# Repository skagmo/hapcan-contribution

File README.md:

HAPCAN contribution
===================

This is a collaboration of work I've done related to my home automation system based on HAPCAN.

HAPCAN is a completely open source home automation system with wired components communicating over CAN bus. It is comparable with KNX, but far cheaper. Due to the open source nature and the use of CAN, it is also much better suited for those interested in making their own modules.

This has no connection with the HAPCAN project, and modules are therefore called "HAPCAN compatible", as they can communicate with HAPCAN devices but are not actual HAPCAN devices. It can rather be seen as a contribution to the HAPCAN community.

--
Jon Petter Skagmo, LA3JPA

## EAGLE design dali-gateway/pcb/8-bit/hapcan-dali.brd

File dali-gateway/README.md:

HAPCAN compatible DALI gateway
==============================

The purpose of this project is to connect a DALI (Digital Addressable Lighting Interface) network with a HAPCAN network, and making it possible to control for example a DALI dimmer by triggering a HAPCAN button module.

Features
--------

Can be indirectly controlled by other CAN nodes. The behaviour is somewhat similar to "memory cells" in HAPCAN, but less flexible due to the differences between HAPCAN and DALI. A given HAPCAN node sending BUTTON frames can indirectly trigger a given DALI address, and enable "Touch DIM" behaviour:

- Short press (under 400 ms): Toggle state of DALI device. As the DALI protocol does not have a toggle command, the gateway keeps track of the state and arc level of all 81 DALI addresses (64 individual, 16 groups, 1 broadcast) to make a DALI dimmer toggle between being off and being set at a given arc level.

- Long press (over 400 ms): Will start dimming the DALI device by sending an arc level command every 100 ms until the button is released, or the maximum or minimum level has been reached.

After the state or arc level of a DALI device has been changed, either through direct or indirect control, the gateway will send the new state and arc level to the CAN bus to update all other nodes.

The gateway can also be directly controlled with an instruction (toggle or set arc level), an arc level (ignored if toggling), and a DALI address.

Firmware project
----------------

The project is written in C for a 32-bit PIC32MX564F128H microcontroller. It is therefore quite different from HAPCAN devices which uses an 8-bit PIC18F26K80, and makes it incompatible with the standard HAPCAN bootloader.

Open the project in Microchip MPLAB X and compile with the XC32 compiler.

| File       | Description |
|:------     |:----------- |
| logic.c    | Contains the gateway logic between DALI and CAN, and HAPCAN related definitions. |
| dali.c     | PIC32 DALI implementation using pin interrupt and timer interrupt. |
| can.c      | CAN initialization and send/receive routines. |

Hardware project
----------------

The schematic and PCB is made in Eagle CAD, and made to fit inside a double DIN rail enclosure similar to those used in the HAPCAN project.

--
Jon Petter Skagmo, LA3JPA, 2016

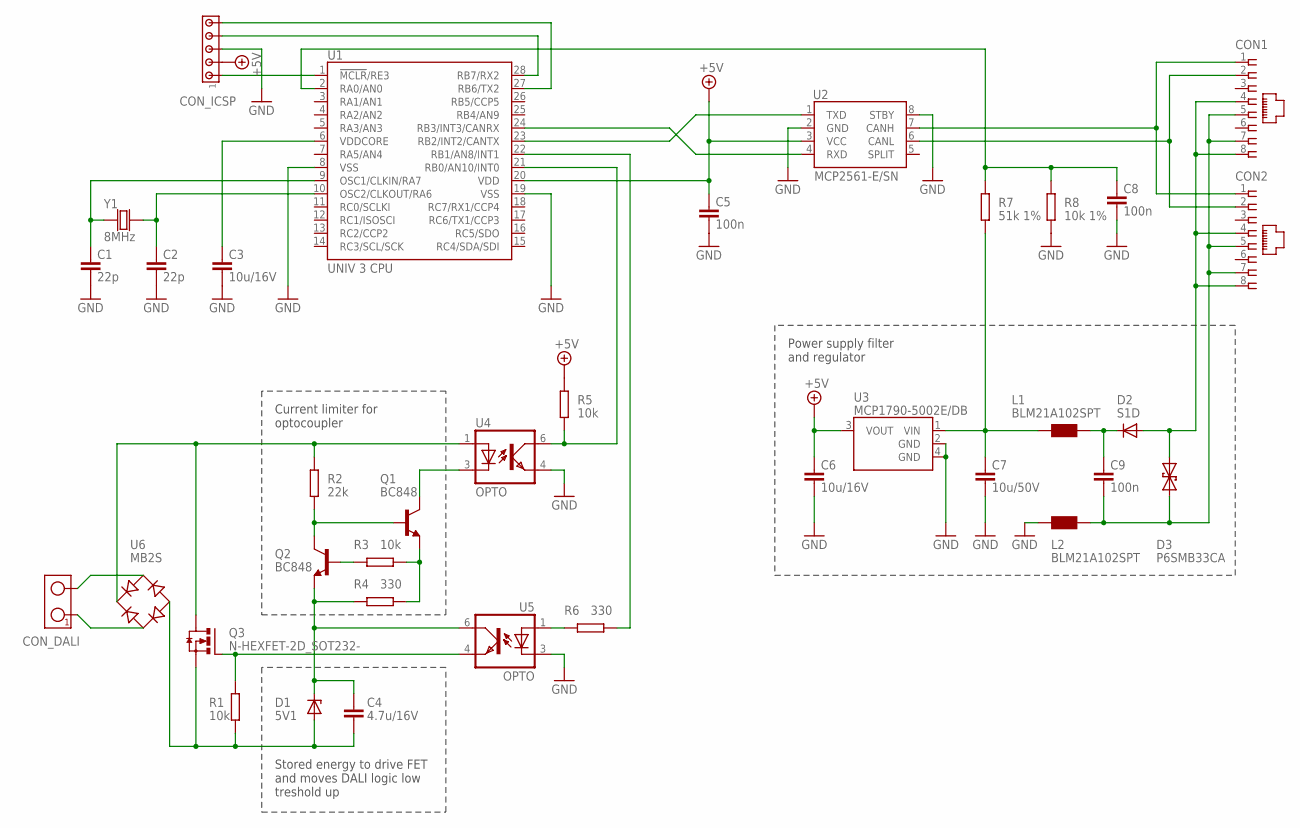
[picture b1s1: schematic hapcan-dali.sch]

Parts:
C1, C2: 22p; 0805
C3, C6: 10u/16V; 0805
C4: 4.7u/16V; 0805
C5, C8, C9: 100n; 0805
C7: 10u/50V; 1210
CON1, CON2: RJ45-SOCKET; RJ45-PCB-SOCKET
CON_DALI: TERMINAL-2; ARK2-5X10,5MM
CON_ICSP: HEADER5; SIP-5
D1: 5V1; SOT23
D2: S1D; DO-214
D3: P6SMB33CA; DO-214_TRANSIL2
L1, L2: BLM21A102SPT; 0805
Q1, Q2: BC848; SOT23
Q3: N-HEXFET-2D_SOT232-; SOT223
R1, R3, R5: 10k; 0805
R2: 22k; 0805
R4, R6: 330; 0805
R7: 51k 1%; 0805
R8: 10k 1%; 0805
U1: UNIV 3 CPU; UNIV3CPU
U2: MCP2561-E/SN; SO-08
U3: MCP1790-5002E/DB; SOT-223
U4, U5: OPTO; TLP185
U6: MB2S; SOIC-4
Y1: 8MHz; CRYSTAL-HC49V

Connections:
+5V: C5.1, C6.1, CON_ICSP.2, R5.1, U1.20 (VDD), U2.3 (VCC), U3.3 (VOUT)
CAN_N: CON1.2, CON2.2, U2.6 (CANL)
CAN_P: CON1.1, CON2.1, U2.7 (CANH)
GND: C1.2, C2.2, C3.2, C5.2, C6.2, C7.2, C8.2, CON_ICSP.3, L2.1, R8.1, U1.8 (VSS), U1.19 (VSS), U2.2 (GND), U2.8 (STBY), U3.2 (GND), U3.4 (GND), U4.4 (EMIT), U5.3 (C)
unnamed: Q1.2 (E), R3.1, R4.2
unnamed: U1.24 (RB3/INT3/CANRX), U2.4 (RXD)
unnamed: U1.23 (RB2/INT2/CANTX), U2.1 (TXD)
unnamed: Q2.1 (B), R3.2
unnamed: C9.1, D2.C, L1.2
unnamed: Q1.1 (B), Q2.3 (C), R2.1
unnamed: C4.2, D1.1 (A), Q3.3 (S), R1.1, U6.-
unnamed: CON_ICSP.1, U1.1 (!MCLR!/RE3)
unnamed: CON1.4, CON1.8, CON2.4, CON2.8, D2.A, D3.C (2)
unnamed: CON_ICSP.4, U1.28 (RB7/RX2)
unnamed: Q1.3 (C), U4.3 (C)
unnamed: CON_ICSP.5, U1.27 (RB6/TX2)
unnamed: C2.1, U1.10 (OSC2/CLKOUT/RA6), Y1.2
unnamed: C8.1, R7.2, R8.2, U1.2 (RA0/AN0)
unnamed: C7.1, L1.1, R7.1, U3.1 (VIN)
unnamed: CON_DALI.1, U6.~1 (AC1)
unnamed: CON_DALI.2, U6.~2 (AC2)
unnamed: R6.1, U1.22 (RB1/AN8/INT1)
unnamed: C9.2, CON1.5, CON1.7, CON2.5, CON2.7, D3.A (1), L2.2
unnamed: Q3.1 (G), R1.2, U5.4 (EMIT)
unnamed: Q3.2 (D), Q3.4 (D), R2.2, U4.1 (A), U6.+
unnamed: R5.2, U1.21 (RB0/AN10/INT0), U4.6 (COL)
unnamed: C4.1, D1.3 (C), Q2.2 (E), R4.1, U5.6 (COL)
unnamed: R6.2, U5.1 (A)
unnamed: C1.1, U1.9 (OSC1/CLKIN/RA7), Y1.1
unnamed: C3.1, U1.6 (VDDCORE)

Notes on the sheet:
Stored energy to drive FET and moves DALI logic low treshold up
Current limiter for optocoupler
Power supply filter and regulator

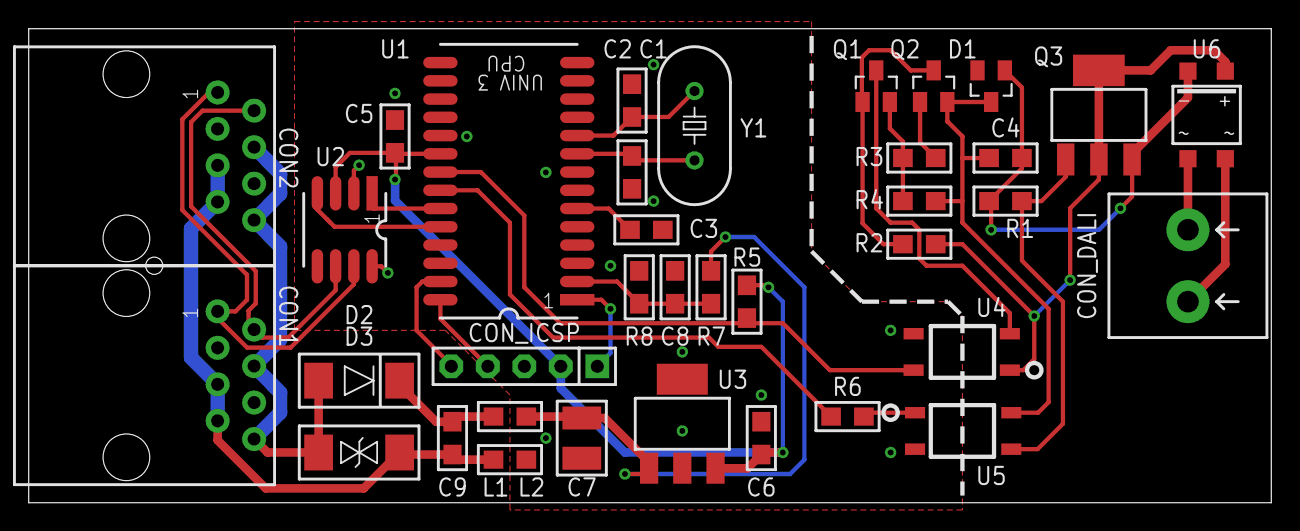
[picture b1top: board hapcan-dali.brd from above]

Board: 4 copper layers, 86.5 x 33.0 mm, 36 parts (0 on the bottom side), 30 nets.

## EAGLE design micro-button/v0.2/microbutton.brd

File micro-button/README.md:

HAPCAN compatible micro button interface
========================================

A firmware compatible re-make of the HAPCAN button module.

I made it because I wanted a board with connectors and smaller outline. Version 2 runs on 3.3 V and uses a small switch mode buck converter to minimize power consumption.

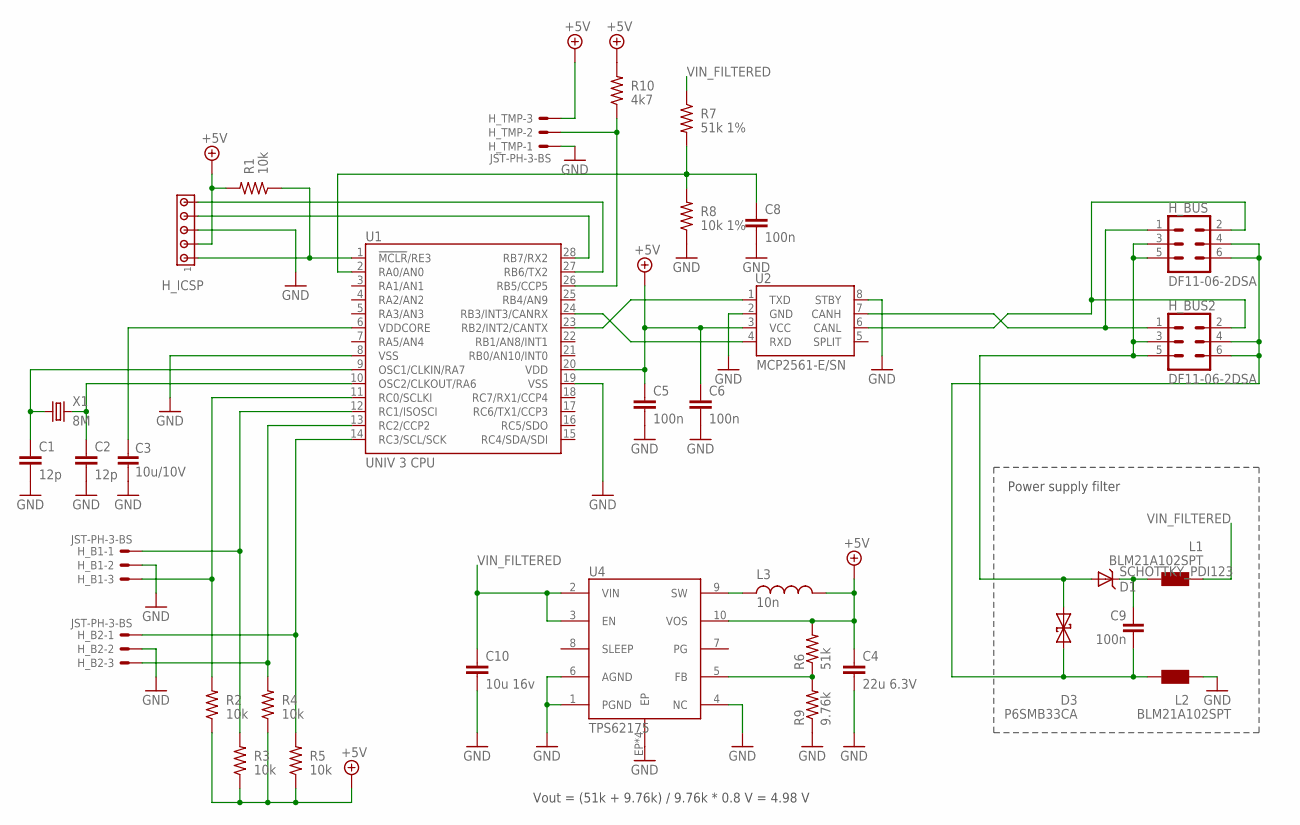
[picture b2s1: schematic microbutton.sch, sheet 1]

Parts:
C1, C2: 12p; 0603
C3: 10u/10V; 0805
C4: 22u 6.3V; 0805
C5, C6, C8: 100n; 0603
C9: 100n; 0805
C10: 10u 16v; 1206
D1: SCHOTTKY_PDI123; POWERDI123
D3: P6SMB33CA; DO-214_TRANSIL2
H_B1, H_B2: JST-PH-3-BS; B3B-PH-K-S
H_BUS, H_BUS2: DF11-06-2DSA; DF11-06DP-2DSA
H_ICSP: HEADER5; SIP-5
H_TMP: JST-PH-3-BS; B3B-PH-K-S
L1, L2: BLM21A102SPT; 0805
L3: 10n; IND-SRN3015
R1, R2, R3, R4, R5: 10k; 0603
R6: 51k; 0603
R7: 51k 1%; 0603
R8: 10k 1%; 0603
R9: 9.76k; 0603
R10: 4k7; 0603
U1: UNIV 3 CPU; UNIV3CPU
U2: MCP2561-E/SN; SO-08
U4: TPS62175; WSON-10
X1: 8M; TXC-7A_HAND

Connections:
+5V: C4.1, C5.1, C6.1, H_ICSP.2, H_TMP.3, L3.P$2 (2), R1.2, R2.1, R3.1, R4.1, R5.1, R6.2, R10.2, U1.20 (VDD), U2.3 (VCC), U4.10 (VOS)
CAN_N: H_BUS.1, H_BUS2.1, U2.7 (CANH)
CAN_P: H_BUS.2, H_BUS2.2, U2.6 (CANL)
GND: C1.2, C2.2, C3.2, C4.2, C5.2, C6.2, C8.2, C10.2, H_B1.2, H_B2.2, H_ICSP.3, H_TMP.1, L2.1, R8.1, R9.1, U1.8 (VSS), U1.19 (VSS), U2.2 (GND), U2.8 (STBY), U4.1 (PGND), U4.4 (NC), U4.6 (AGND), U4.EP, U4.V1 (EP), U4.V2 (EP), U4.V3 (EP)
unnamed: H_B1.3, R2.2, U1.11 (RC0/SCLKI)
unnamed: U1.24 (RB3/INT3/CANRX), U2.4 (RXD)
unnamed: U1.23 (RB2/INT2/CANTX), U2.1 (TXD)
unnamed: H_B1.1, R3.2, U1.12 (RC1/ISOSCI)
unnamed: C9.1, D1.C, L1.2
unnamed: H_B2.3, R4.2, U1.13 (RC2/CCP2)
unnamed: H_B2.1, R5.2, U1.14 (RC3/SCL/SCK)
unnamed: H_ICSP.1, R1.1, U1.1 (!MCLR!/RE3)
unnamed: D1.A, D3.C (2), H_BUS.3, H_BUS.5, H_BUS2.3, H_BUS2.5
unnamed: H_ICSP.4, U1.28 (RB7/RX2)
unnamed: H_TMP.2, R10.1, U1.26 (RB5/CCP5)
unnamed: L3.P$1 (1), U4.9 (SW)
unnamed: R6.1, R9.2, U4.5 (FB)
unnamed: H_ICSP.5, U1.27 (RB6/TX2)
unnamed: C2.1, U1.10 (OSC2/CLKOUT/RA6), X1.2
unnamed: C8.1, R7.2, R8.2, U1.2 (RA0/AN0)
unnamed: C9.2, D3.A (1), H_BUS.4, H_BUS.6, H_BUS2.4, H_BUS2.6, L2.2
unnamed: C1.1, U1.9 (OSC1/CLKIN/RA7), X1.1
unnamed: C3.1, U1.6 (VDDCORE)
VIN_FILTERED: C10.1, L1.1, R7.1, U4.2 (VIN), U4.3 (EN)

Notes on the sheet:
Power supply filter
Vout = (51k + 9.76k) / 9.76k * 0.8 V = 4.98 V

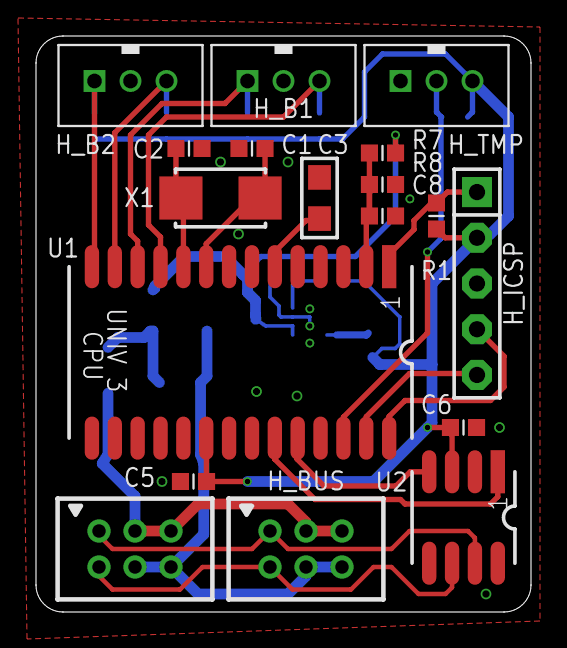
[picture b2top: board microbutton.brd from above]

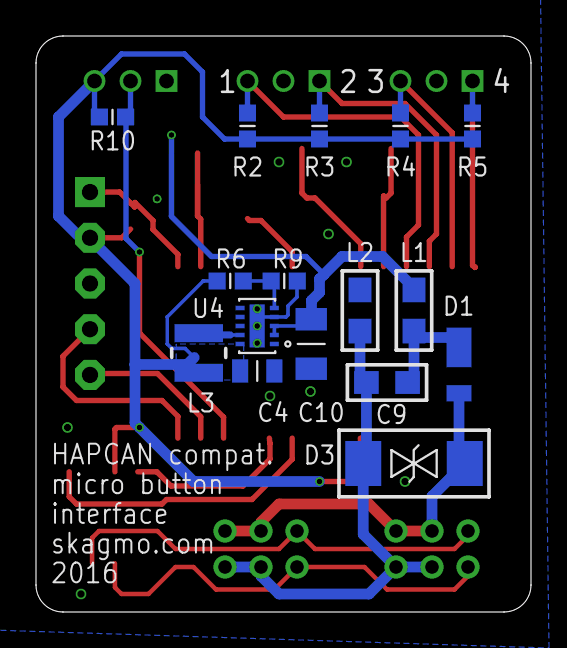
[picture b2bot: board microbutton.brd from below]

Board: 4 copper layers, 27.5 x 32.0 mm, 34 parts (16 on the bottom side), 24 nets.

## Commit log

2017-02-12 Added gitignore
2017-02-12 Fixed gitignore

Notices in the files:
parts and their libraries:
SparkFun: Licensing: CC v3.0 Share-Alike You are welcome to use this library for commercial purposes.
